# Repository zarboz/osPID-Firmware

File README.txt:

/********************************************************
 * osPID Firmware, for Arduino PID Shield, v1.0.0
 * original code by Brett Beauregard & Rocket Scream
 * additional code by Benjamin K. Stuhl and Tom Price
 * License: GPLv3 & BSD License (For autotune)
 * November 2013
 * modifications to impliment autotune and intelliLCD 
 * License Apache & BSD license by Bryan Smith
 ********************************************************/

This code is a variant of the original osPID firmware, written by Brett Beauregard and
Rocket Scream and revamped by Benjamin K. Stuhl. It was created for the stripboard
Arduino PID controller shield and has been adapted to reflect the new hardware. It also
features numerous extensions and updates. IntelliLCD addition made by Bryan Smith wich will
allow user to tell current temp against goal temp with color of RGB LCD display.

License for IntelliLCD
 License Summary

License does not expire.
Can be used on unlimited sites, servers
Source-code or binary products cannot be resold or distributed
Commercial use allowed under the following conditions :
Only To be used by Dabper ENAILS aside from the OSPID code this is original work and is to be treated as such
Cannot modify source-code for any purpose (cannot create derivative works)
Attribution to software creator must be made as specified:
mugenman1111@gmail.com
 For more information on the license summary topics
 Terms and conditions

Preamble: This Agreement, signed on Aug 19, 2014 [hereinafter: Effective Date] governs the relationship between Bryan Smith, a Business Entity, (hereinafter: Licensee) and DabPer enail , a Partnership under the laws of CO, United States whose principal place of business is CO, United States (Hereinafter: Licensor). This Agreement sets the terms, rights, restrictions and obligations on using [IntelliLCD] (hereinafter: The Software) created and owned by Licensor, as detailed herein
License Grant: Licensor hereby grants Licensee a Personal, Non-assignable & non-transferable, Commercial with terms, Without the rights to create derivative works, Non-exclusive license, all with accordance with the terms set forth and other legal restrictions set forth in 3rd party software used while running Software.
Limited: Licensee may use Software for the purpose of:
Running Software on Licensees Website[s] and Server[s];
Allowing 3rd Parties to run Software on Licensees Website[s] and Server[s];
Publishing Softwares output to Licensee and 3rd Parties;
Distribute verbatim copies of Softwares output (including compiled binaries);
Modify Software to suit Licensees needs and specifications.
Binary Restricted: Licensee may sublicense Software as a part of a larger work containing more than Software, distributed solely in Object or Binary form under a personal, non-sublicensable, limited license. Such redistribution shall be limited to unlimited codebases.
Non Assignable & Non-Transferable: Licensee may not assign or transfer his rights and duties under this license.
Commercial use allowed with restrictions: Only To be used by Dabper ENAILS aside from the OSPID code this is original work and is to be treated as such
With Attribution Requirements?: mugenman1111@gmail.com
Term & Termination: The Term of this license shall be until terminated. Licensor may terminate this Agreement, including Licensees license in the case where Licensee :
became insolvent or otherwise entered into any liquidation process; or
exported The Software to any jurisdiction where licensor may not enforce his rights under this agreements in; or
Licensee was in breach of any of this license's terms and conditions and such breach was not cured, immediately upon notification; or
Licensee in breach of any of the terms of clause 2 to this license; or
Licensee otherwise entered into any arrangement which caused Licensor to be unable to enforce his rights under this License.
Payment: In consideration of the License granted under clause 2, Licensee shall pay Licensor a fee, via Credit-Card, PayPal or any other mean which Licensor may deem adequate. Failure to perform payment shall construe as material breach of this Agreement.
Upgrades, Updates and Fixes: Licensor may provide Licensee, from time to time, with Upgrades, Updates or Fixes, as detailed herein and according to his sole discretion. Licensee hereby warrants to keep The Software up-to-date and install all relevant updates and fixes, and may, at his sole discretion, purchase upgrades, according to the rates set by Licensor. Licensor shall provide any update or Fix free of charge; however, nothing in this Agreement shall require Licensor to provide Updates or Fixes.
Upgrades: for the purpose of this license, an Upgrade shall be a material amendment in The Software, which contains new features and or major performance improvements and shall be marked as a new version number. For example, should Licensee purchase The Software under version 1.X.X, an upgrade shall commence under number 2.0.0.
Updates: for the purpose of this license, an update shall be a minor amendment in The Software, which may contain new features or minor improvements and shall be marked as a new sub-version number. For example, should Licensee purchase The Software under version 1.1.X, an upgrade shall commence under number 1.2.0.
Fix: for the purpose of this license, a fix shall be a minor amendment in The Software, intended to remove bugs or alter minor features which impair the The Software's functionality. A fix shall be marked as a new sub-sub-version number. For example, should Licensee purchase Software under version 1.1.1, an upgrade shall commence under number 1.1.2.
Support: Software is provided under an AS-IS basis and without any support, updates or maintenance. Nothing in this Agreement shall require Licensor to provide Licensee with support or fixes to any bug, failure, mis-performance or other defect in The Software.
Bug Notification: Licensee may provide Licensor of details regarding any bug, defect or failure in The Software promptly and with no delay from such event; Licensee shall comply with Licensor's request for information regarding bugs, defects or failures and furnish him with information, screenshots and try to reproduce such bugs, defects or failures.
Feature Request: Licensee may request additional features in Software, provided, however, that (i) Licensee shall waive any claim or right in such feature should feature be developed by Licensor; (ii) Licensee shall be prohibited from developing the feature, or disclose such feature request, or feature, to any 3rd party directly competing with Licensor or any 3rd party which may be, following the development of such feature, in direct competition with Licensor; (iii) Licensee warrants that feature does not infringe any 3rd party patent, trademark, trade-secret or any other intellectual property right; and (iv) Licensee developed, envisioned or created the feature solely by himself.
Liability:  To the extent permitted under Law, The Software is provided under an AS-IS basis. Licensor shall never, and without any limit, be liable for any damage, cost, expense or any other payment incurred by Licensee as a result of Softwares actions, failure, bugs and/or any other interaction between The Software  and Licensees end-equipment, computers, other software or any 3rd party, end-equipment, computer or services.  Moreover, Licensor shall never be liable for any defect in source code written by Licensee when relying on The Software or using The Softwares source code.
Warranty:  
Intellectual Property: Licensor hereby warrants that The Software does not violate or infringe any 3rd party claims in regards to intellectual property, patents and/or trademarks and that to the best of its knowledge no legal action has been taken against it for any infringement or violation of any 3rd party intellectual property rights.
No-Warranty: The Software is provided without any warranty; Licensor hereby disclaims any warranty that The Software shall be error free, without defects or code which may cause damage to Licensees computers or to Licensee, and that Software shall be functional. Licensee shall be solely liable to any damage, defect or loss incurred as a result of operating software and undertake the risks contained in running The Software on Licenses Server[s] and Website[s].
Prior Inspection: Licensee hereby states that he inspected The Software thoroughly and found it satisfactory and adequate to his needs, that it does not interfere with his regular operation and that it does meet the standards and scope of his computer systems and architecture. Licensee found that The Software interacts with his development, website and server environment and that it does not infringe any of End User License Agreement of any software Licensee may use in performing his services. Licensee hereby waives any claims regarding The Software's incompatibility, performance, results and features, and warrants that he inspected the The Software.
No Refunds: Licensee warrants that he inspected The Software according to clause 7(c) and that it is adequate to his needs. Accordingly, as The Software is intangible goods, Licensee shall not be, ever, entitled to any refund, rebate, compensation or restitution for any reason whatsoever, even if The Software contains material flaws.
Indemnification: Licensee hereby warrants to hold Licensor harmless and indemnify Licensor for any lawsuit brought against it in regards to Licensees use of The Software in means that violate, breach or otherwise circumvent this license, Licensor's intellectual property rights or Licensor's title in The Software. Licensor shall promptly notify Licensee in case of such legal action and request Licensees consent prior to any settlement in relation to such lawsuit or claim.
Governing Law, Jurisdiction: Licensee hereby agrees not to initiate class-action lawsuits against Licensor in relation to this license and to compensate Licensor for any legal fees, cost or attorney fees should any claim brought by Licensee against Licensor be denied, in part or in full.

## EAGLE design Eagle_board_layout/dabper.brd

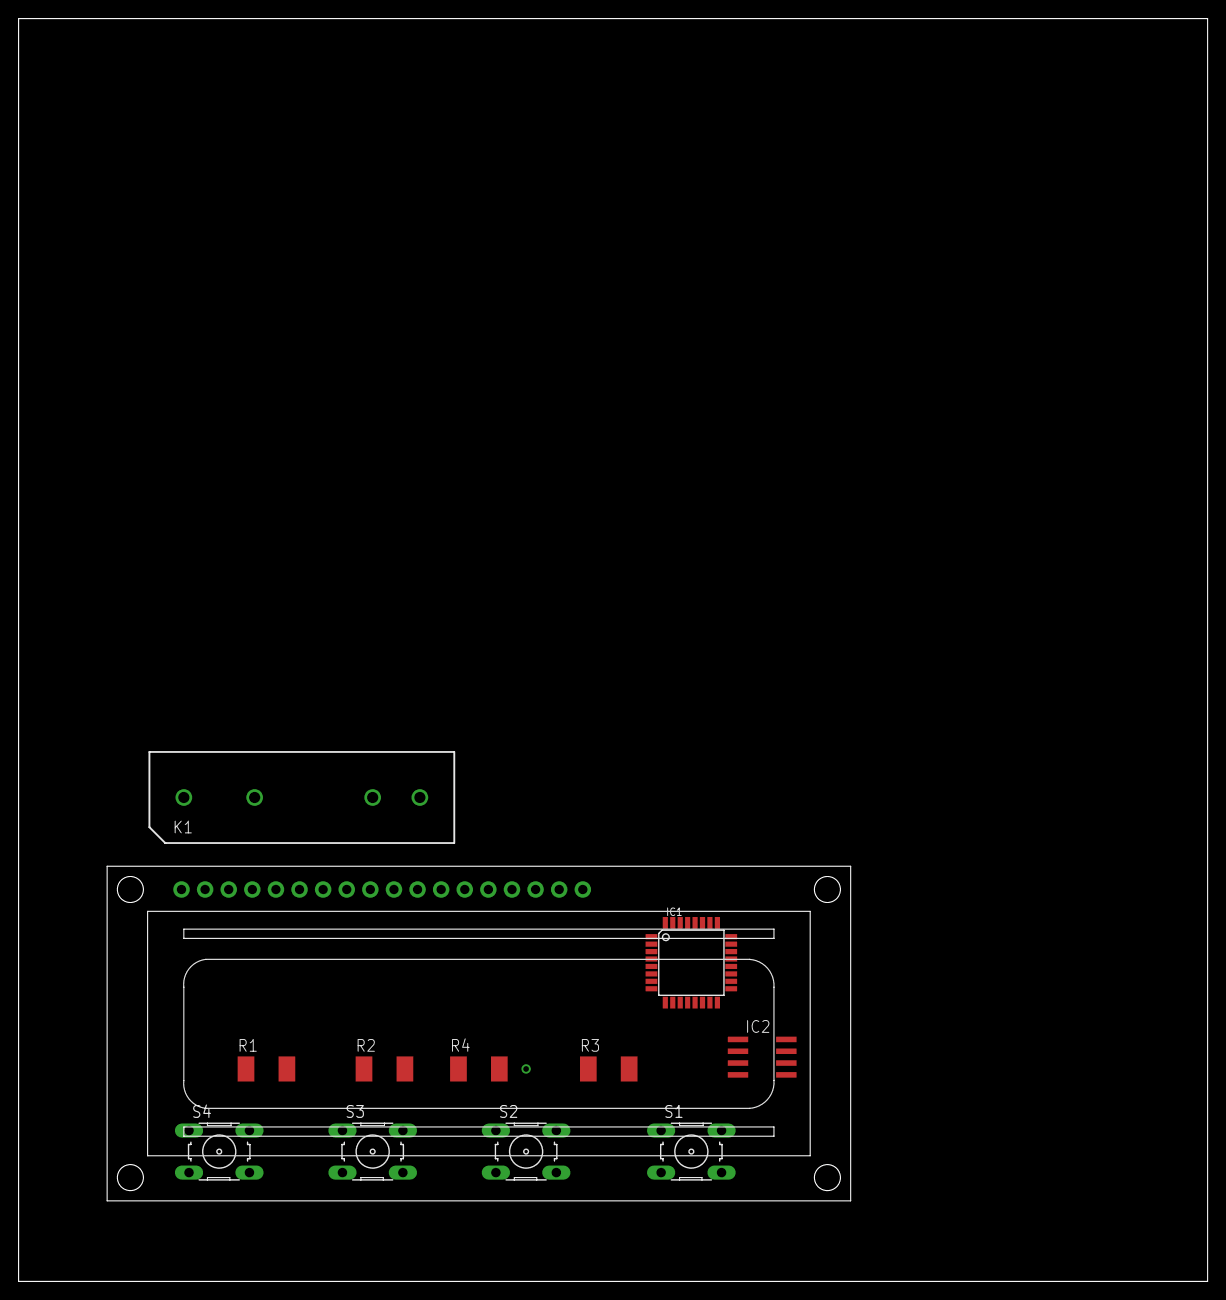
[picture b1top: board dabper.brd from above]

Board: 2 copper layers, 127.9 x 135.9 mm, 12 parts (0 on the bottom side), 15 nets.

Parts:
IC1: ATMEGA328-AU; TQFP32-08
IC2: MAX31855; SOIC8
K1: AQ1AD2-3; AQ1
R1, R4: 1K Ohm; R5025
R2: 470 Ohm; R5025
R3: 330 Ohm; R5025
S1: Switch 1; B3F-10XX
S2: Switch 2; B3F-10XX
S3: Switch 3; B3F-10XX
S4: Switch 4; B3F-10XX
U$1: HD44780LCD_RGBLONGPINS; LCD1602-RGB

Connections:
unnamed: IC1.27, R3.2, R4.1, S4.1
unnamed: R2.2, R3.1, S3.1
unnamed: R1.2, R2.1, S2.1
unnamed: R1.1, S1.1
unnamed: IC1.5, IC2.1, S1.2, S2.2, S3.2, S4.2, U$1.3, U$1.5
unnamed: IC1.23, IC2.7
unnamed: IC1.25, IC2.5
unnamed: IC1.24, IC2.6
unnamed: IC1.10, IC1.15, U$1.12, U$1.18
unnamed: IC1.13, IC1.14, U$1.16, U$1.17
unnamed: IC1.1, IC1.2, U$1.6, U$1.14
unnamed: IC1.9, U$1.13
unnamed: IC1.11, U$1.11
unnamed: IC1.26, K1.2
VSS: IC1.4, IC1.32, IC2.4, R4.2, U$1.1, U$1.4, U$1.15

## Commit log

2013-10-02 DIY buzzer code and minor edits to save space
    shaving serial messages
    remember, no virtual methods
    array of settings for input sensors
    hard coded controller name
    intermittent buzzer
    osPID_serial.ino edits
2013-10-03 baudrate
2013-10-03 removed MyLiquidCrystal class
2013-10-04 minor changes to osPID_Menu.ino
2013-10-04 commented out ospAsserts
2013-10-04 commented out BUGCHECKs
2013-10-04 fixed alarm
2013-10-04 reordered config menu items
2013-10-05 ospAssert and BUGCHECK under compile flag not commented out
2013-10-05 3 character icons
2013-10-06 Fixed output, window size display
2013-10-07 fixed input refresh
2013-10-07 updated to AutoTune library version 0.0.1
2013-10-07 PI controller compile option
2013-10-07 observe output limits when setting autotune step
2013-10-07 clear EEPROM if units have changed
2013-10-08 acknowledge serial commands
2013-10-08 reduced number of baud rate options
2013-10-09 some changes to serial commands
2013-10-12 modifications after first pass of front end code
2013-10-12 fixup serial communication for profiles
2013-10-19 debugging of serial communication complete except for profile definition/running
2013-10-20 power on option
2013-10-30 removed baudrate menu, added auto tune method and command
2013-11-01 auto tune defaults in configuration file
2013-11-01 modified auto tune library
2013-11-01 correction to calculation of Pu, tuning rule table
2013-11-01 squeezed PID_v1.cpp
2013-11-02 some fixed point inputs for PID & AutoTune methods
2013-11-02 inputType and outputType now Device class variables not global
2013-11-03 workaround Arduino auto-prototyping fail
2013-11-03 rejigged menus to be more like GUI
2013-11-04 fixed point lookback array
2013-11-05 tuning variable moved from global to Class PID
    global ctrlDirection flag removed
    removed global flag modeIndex
2013-11-05 autotune as PID method
2013-11-08 html documentation
2013-11-08 baudrate compile option
2013-11-28 attempted workaround for Leonardo
2013-12-03 compiled versions for Uno
2014-07-02 Staging changes for display name
    Adding my name to authors and changing display name for board on boot to
    fit my application
2014-07-07 updating README
2014-08-04 Removing old liquidcrystal library call outs updating pinout of new RGB LCD adapting code for new display
2014-08-04 fixing some lcd definitions that were broken by me
2014-08-04 changing naming convention of LCD panel from theLCD to lcd
2014-08-04 updating commenting on config
2014-08-04 Removing misc shit we don't really need from our repo
2014-08-08 resolving the RGB LCD issue and adding nifty swirl of color on boot
2014-08-08 add button diagram for wiring schematic
2014-08-12 fixing pinoutissue
2014-08-12 fixup Colors on boot and fixup set color background
2014-08-12 update max31855 drivers to adafruit
2014-08-12 updating 31855 drivers
2014-08-12 Updated Max31855 with adafruits drivers
2014-08-12 inital RGB reading from k type thermocouple code
2014-08-12 Update 31855 driver
2014-08-18 Updating code i placed to see if file was being compiled
2014-08-18 Staging RGB colorshift on temp input code right now it is very rudimentary and does no number compare
2014-08-19 Adding in color smoothing to IntelliLCD code. coding trip points in for IntelliLCD next is to assign variables for input colors on trip point
2014-08-19 removing commenting updating licensing for IntelliLCD
2014-08-19 Cleaning up the tree
2014-08-20 removing commenting and updating color fade code to trip points instead of fade again
2014-08-21 adding beta PCB board design
2014-08-22 adding buttons and finalizing parts needed on PCB
2014-08-27 removing buzzer code and fixing PID gain coefficients
2014-08-29 Fixup menu cycle selection timing to a two decimal point scaling and allow less than 1 second cycle. Alter color scheme for triggering intelliLCD so that when sensor is unplugged LCD will pulse purpl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
2014-08-29 Changing boot logo
2014-08-29 final naming cleanup and decimal place correction
2014-08-29 final changes before headed out to the bossmans house
2014-09-14 fixing PID failure
2014-12-01 enable RGB lcd from adafruit
2014-12-01 make trinket friendly
2015-02-25 fixing custom color menu as its not done yet and changing device name to be more fitting
